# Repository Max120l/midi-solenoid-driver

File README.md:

# midi-solenoid-driver — direct MIDI fork

A fork of [willemcvu/midi-solenoid-driver](https://github.com/willemcvu/midi-solenoid-driver)
that lets the solenoid driver board accept **standard MIDI directly**, with no
interface board in between, and adds **peak-and-hold** solenoid drive,
**selectable MIDI channel**, **optional velocity response**, and **defensive
handling of badly-formed MIDI**.

All hardware in this repository — the driver PCB, the schematics, the gerbers,
the photographs — is Willem Hillier's original work, unchanged. This fork only
replaces the firmware that runs on it.

---

## Why this fork exists

The upstream project is a driver board plus a companion USB-to-serial interface
board. The driver board doesn't speak MIDI; it speaks 38400-baud MIDI-*like*
serial, and the interface board is what turns real MIDI into that. Upstream's
interface work stalled — the `wifi_native_midi` firmware is committed as "not
working" and the repository has had no commits since October 2020. Attempts to
reach the original author about it went unanswered.

Rather than finish the missing interface board, this fork moves the job onto the
driver board itself. The ATmega328PB decodes 31250-baud MIDI on the same RJ12
input pin using the Arduino MIDI Library, so a MIDI source connects straight to
the driver board.

## What's different

| | Upstream `midiSolenoidDriver` | This fork's `midiSolenoidDriverDirectMIDI` |
|---|---|---|
| Input | 38400 baud MIDI-over-serial, needs the interface board | 31250 baud standard MIDI, direct |
| Parsing | Hand-rolled byte-by-byte state machine | Arduino MIDI Library on the hardware UART |
| Running status | Mishandled | Handled |
| Solenoid drive | Full current for the whole note | Peak-and-hold, phase-staggered across channels |
| Velocity | Ignored | Optionally scales pull-in time |
| Note offset | 7-bit DIP switch, 1-note steps | Same, plus a 3-switch fallback mode |
| MIDI channel | 4-bit analog DIP switch | Fixed, DIP-read, or omni |
| Malformed MIDI | Notes can stick on | All-notes-off, stop, reset, and a stuck-note watchdog |

Upstream's original firmware is still here, untouched, in
[`firmware/midiSolenoidDriver/`](firmware/midiSolenoidDriver/). If you have the
USB interface board and it works for you, use that one.

## Hardware

Unchanged from upstream. See [`README-upstream.md`](README-upstream.md) for the
original project description, board photos, and daisy-chaining details.

- Driver board: [`hardware/midi-solenoid-driver/`](hardware/midi-solenoid-driver/)
- MCU: ATmega328PB
- 16 solenoid outputs, "OUTPUTS 1-16" on the silkscreen

[`hardware/HARDWARE-NOTES.md`](hardware/HARDWARE-NOTES.md) records how both DIP
switch blocks are actually wired -- including why the small block shows only two
GPIO connections on a multimeter, and why switch 8 of the large block does
nothing -- and how to deal with the schematic's missing symbol cache.

### MIDI input wiring

MIDI arrives on **pin 0 (RXD0)**, the ATmega's hardware UART receive pin — the
same pin upstream used. Feed it a **conventional, non-inverted MIDI signal**:
idle high, standard UART polarity, which is what a correctly-wired optocoupler
front end produces.

If your input idles *low*, the signal is inverted and the UART will never frame
a byte — it sees a permanent break condition. **The symptom is total silence:
the board boots, runs its exercise routine, and ignores every note.** The right
fix is the wiring, but there is an escape hatch for testing:

```cpp
#define MIDI_INPUT_POLARITY MIDI_INPUT_INVERTED
```

The AVR's USART has no receive-invert bit, so inverting in firmware means
abandoning the hardware UART for `SoftwareSerial` in inverse-logic mode.

**Treat that as a bench workaround, not a destination.** `SoftwareSerial`
receives each byte by busy-waiting through it with interrupts disabled — about
320 µs at 31250 baud, which at 8 MHz is a quarter of the CPU's entire budget
for that stretch. A byte arriving during another byte is lost, which is exactly
what dense MIDI produces, and `loop()` stalls meanwhile so the hold PWM gets
rougher too. Costs about 500 bytes of flash. Fine for proving a few notes;
not what you want under a full chest.

#### Fixing it in hardware instead

Invert the signal before it reaches pin 0 and you keep the hardware UART.
Speed is irrelevant here — a bit is 32 µs at 31250 baud, so any logic family
has thousands of times the margin it needs. Choose for signal quality:

- **74HC14**, a Schmitt-trigger hex inverter. The best pick: it inverts *and*
  squares up the lazy edges an optocoupler with a large pull-up tends to
  produce.
- **74HCT04** if you would rather not use a Schmitt — CMOS input currents with
  TTL-compatible thresholds.
- **A single NPN transistor**, which is usually already in the drawer:

```
  opto out ──[4.7k]──┬── B                      +5V
                     │                           │
                   [10k]      2N3904           [1k]
                     │        E ── GND           │
                    GND       C ─────────────────┴──── to pin 0 (RXD0)
```

The 10k from base to ground matters more than it looks: it holds the
transistor off if the input ever floats, so the output idles **high** — which
a UART reads as "no data" rather than as a break condition.

Tie unused gate inputs of a logic IC to GND or Vcc; floating CMOS inputs
oscillate. Power either option from the board's own 5 V rail.

To verify before connecting: with MIDI idle and nothing playing, the inverter
output should sit **high**, near 5 V. If it idles low, it is still inverted.

The firmware disables the UART **transmitter** while keeping the receiver:

```cpp
UCSR0B &= ~(1 << TXEN0);
```

Several boards share the RJ12 line, and none of them should be able to drive
it. Upstream does the same thing for the same reason. Two consequences worth
knowing:

- **There is no serial debug output.** If you want `Serial.print` while
  bench-testing, comment that line out — but do not do so with the board
  connected to a shared bus, because it will fight every other board on it.
- It also frees pin 1 to be read as a DIP switch input, which is why the
  switches are configured *after* the UART in `setup()`.

Flashing over the bootloader still works normally.

## Configuration

Everything configurable sits in one block at the top of the sketch. It comes
in two kinds: **build-time choices** — which switches mean what, where the MIDI
channel comes from, input polarity — that describe the hardware and need a
reflash to change; and **tuning parameters** — pull-in and hold drive, the
watchdog, the exercise routine — that describe the instrument and are
**adjustable at runtime over MIDI**, see
[Runtime configuration over MIDI](#runtime-configuration-over-midi). The values
in the sketch for the second kind are compiled defaults, not the last word.

### Note offset — which 16 notes this board plays

```cpp
#define NOTE_OFFSET_MODE OFFSET_COARSE3
```

| Mode | Switches used | Steps | Use when |
|---|---|---|---|
| `OFFSET_FULL7` | all 7 of the large DIP block | 1 note | Normal, undamaged hardware |
| `OFFSET_COARSE3` | switches 1-3 only | 16 notes | The other four switches are dead |

**This fork defaults to `OFFSET_COARSE3`**, because the boards it is maintained
against have a damaged large DIP block with only three working switches. If
your switches are all good — which they should be on a board you have just
built — set `OFFSET_FULL7` instead. Nothing else needs to change.

`OFFSET_FULL7` is upstream's mapping, restored: switches 1-7 are worth
+1, +2, +4, +8, +16, +32, +64 respectively, active-low, so any base note from
0 to 127 is reachable. The board responds to `baseNote` through
`baseNote + 15`.

`OFFSET_COARSE3` re-weights the three surviving switches to +16, +32 and +64,
giving base notes 0, 16, 32 … 112. One board's worth of notes per step, so a
chain can still address the whole keyboard — just not at arbitrary offsets.

### MIDI channel

```cpp
#define CHANNEL_SOURCE CHANNEL_FIXED
const byte fixedChannel = 1;
```

| Mode | Behaviour |
|---|---|
| `CHANNEL_FIXED` | Uses `fixedChannel`, 1-16 |
| `CHANNEL_DIP` | Reads the 4-bit small DIP block, upstream's `readSmallDip()` ported back |
| `CHANNEL_OMNI` | Responds on every channel |

`CHANNEL_DIP` reads two analog pins, two switches each, using upstream's
voltage thresholds — that block isn't wired to four digital pins. Upstream's
mapping is 0-indexed; this firmware adds 1, so the switches read as the channel
number your DAW displays.

### Velocity response

```cpp
#define VELOCITY_SOURCE VELOCITY_OFF
```

| Mode | Behaviour | Needs |
|---|---|---|
| `VELOCITY_OFF` | Every note gets the full pull-in time | — |
| `VELOCITY_ON` | Pull-in time scales with velocity | — |
| `VELOCITY_SMALLDIP` | Read one bit of the small DIP block at boot | Channel not from the small DIP |
| `VELOCITY_SWITCH` | Read large-DIP switch 4 (pin 18) at boot | `OFFSET_COARSE3` |

When enabled, velocity scales the pull-in time between `peakDurationMin`
(15 ms) and `peakDurationMax` (40 ms). Harder notes pull in for longer and
therefore hit harder — meaningful on a struck instrument, meaningless on an
organ valve, which is simply open or shut. Hence the default of off.

**If you want velocity on a physical switch, `VELOCITY_SMALLDIP` is normally
the one to use.** Under `OFFSET_FULL7` every switch of the large DIP block is
part of the note offset, so there is no spare one there — but if the MIDI
channel is fixed in firmware, the whole small DIP block is idle, and
`velocitySmallDipBit` picks which of its four switches to read.

`VELOCITY_SWITCH` is the alternative for a board running `OFFSET_COARSE3`,
where large-DIP switches 4-7 are unused anyway.

These constraints are enforced at compile time. Asking for `VELOCITY_SWITCH`
alongside `OFFSET_FULL7`, or `VELOCITY_SMALLDIP` alongside `CHANNEL_DIP`, fails
the build with a message telling you which switches collided — rather than
flashing cleanly and behaving strangely on the bench.

### Stuck-note watchdog

```cpp
30,    // maxNoteSeconds   -- in factoryDefaults; runtime: CC 24, 0 disables
```

Any solenoid held longer than this is force-released. Set to `0` to disable —
but understand what you are turning off: with the watchdog disabled, one
missing note-off leaves a valve open until you power-cycle the board. 30
seconds is longer than almost any real note. Raise it if your music genuinely
holds notes longer than that.

### Power-up valve exercise

```cpp
2,     // exerciseCycles   -- in factoryDefaults; runtime: CC 25, 0 disables
const int exerciseOnTime  = 60;  // ms energised
const int exerciseOffTime = 60;  // ms released
```

Fires every output in turn at boot, at full power, before wind is applied.

The point is **pluck** — the adhesion between a valve and its seat after the
instrument has sat closed. On a lightly loaded valve this can be the largest
single force the solenoid has to overcome, and it is worst on the very first
cycle after a rest, which is exactly the note you least want to fail. Working
the valves loose while the chest is unpressurised costs nothing and no pipe
speaks.

It is sequential rather than simultaneous on purpose. One solenoid at a time
draws a sixteenth of the current, and you hear each output fire in order — so a
dead channel, a swapped connector or a stuck valve announces itself at every
power-up. It doubles as a power-on self test.

Full power is used regardless of `peakDutyPercent`, since breaking stiction is
the one job that genuinely wants maximum force, and one-at-a-time makes the
current draw trivial.

The defaults take `2 × 16 × 120 ms` ≈ **3.8 seconds**. The UART is unattended
during that time, so the receive buffer is discarded afterwards to stop a
part-received message sounding a note the instant the loop opens. Set
`exerciseCycles` to 0 to disable, in which case the shorter boot heartbeat runs
instead and the whole routine is optimised out of the build.

### Runtime configuration over MIDI

The tuning parameters are adjustable while the boards run, by control changes
on a **dedicated configuration channel**, and can be saved to each board's
EEPROM so they survive a power cycle. A board built into an instrument never
needs reflashing to retune it. The Pi-side tool is
[`tools/organ-config/`](tools/organ-config/):

```bash
python organ_config.py --port "USB MIDI" --peak 60 --hold 25 --save
```

| CC | Setting | Range on the wire | Firmware clamps to |
|---|---|---|---|
| 20 | select board | 0–112 = the board with that base note; 113–127 = all | |
| 21 | `peakDutyPercent` | 0–127 | 1–100 |
| 22 | `holdDutyPercent` | 0–127 | 0–`HOLD_DUTY_MAX_PERCENT` (40) |
| 23 | `peakDurationMs` | 0–127 | 1–`PEAK_DURATION_MAX_MS` (127) |
| 24 | `maxNoteSeconds` | 0–127 | as sent; 0 disables the watchdog |
| 25 | `exerciseCycles` | 0–127 | 0–`EXERCISE_CYCLES_MAX` (10) |
| 26 | command | 1 save · 2 reload · 3 factory | |

All on `CONFIG_CHANNEL`, which is **16**; music is on channel 1. That
separation is what stops a stray CC inside a song from retuning the organ
mid-piece — and the arranger's output contains no CCs at all regardless.
Panic messages (CC 120 and 123) are honoured on *every* channel.

**Changes take effect immediately, including on notes already sounding.** That
is deliberate, and it is what makes tuning by ear possible: hold a chord and
step the hold duty down until a valve drops out, back off, save.

**The clamps are the safety.** The boards cannot transmit, so they cannot
report that a value would cook the coils — they can only refuse it. Every
value, whether it arrives by MIDI or is read back from EEPROM, passes through
the same clamps, and the ceilings are compile-time constants sized for
duty-limited solenoids. Raise them only for coils rated for it.

**Save is explicit, and acknowledged.** Settings live in RAM until command 1
writes them to EEPROM — EEPROM has a finite number of writes and live tuning
would otherwise chew through it. A save is acknowledged by a click on output 1
if that output is idle; under wind, a chirp from the board's lowest pipe, and
four boards saving together answer as a four-note chord. Set `CONFIG_ACK` to 0
for silence. At power-up a board loads its EEPROM record if the magic number,
layout version and checksum all agree, and the compiled defaults otherwise.

**A board selection expires.** CC 20 with a base note makes only that board
listen; it reverts to all boards after a quiet minute, so a forgotten selection
cannot strand one. In practice, with identical solenoids on every board, you
address all of them.

`CONFIG_ENABLED 0` compiles the whole layer out, saving about 650 bytes.

## Daisy-chaining several boards

Boards chain over RJ12 and all see the same MIDI stream. Each one is told which
16 notes are *its* by its DIP switches. All boards run identical firmware.

A four-board chain under the default `OFFSET_COARSE3`, covering MIDI notes
48-111 (C3 to D#8). Base notes are limited to multiples of 16, which is exactly
one board's worth, so four boards tile without gaps:

| Board | Base note | Notes covered | Switches closed |
|---|---|---|---|
| 1 | 48 | 48-63 | 1, 2 |
| 2 | 64 | 64-79 | 3 |
| 3 | 80 | 80-95 | 1, 3 |
| 4 | 96 | 96-111 | 2, 3 |

This instrument's chain sits one step lower than that table: board 1 with
every switch open at base note **0**, then 16, 32 and 48, so solenoid *N*
(numbered 1–64, as on the layout sheet) fires on MIDI note *N − 1*. The
arranger's definition, `tools/organ-arranger/instrument/organ.yaml`, records
that as `solenoid_1_note: 0` and does the subtraction itself; the table above
is the same idea shifted up three octaves.

The same chain under `OFFSET_FULL7`, where any base note is reachable — here
placed at 36-99 (C2 to D#7) instead:

| Board | Base note | Notes covered | Switches closed |
|---|---|---|---|
| 1 | 36 | 36-51 | 6, 3 |
| 2 | 52 | 52-67 | 6, 5, 3 |
| 3 | 68 | 68-83 | 7, 3 |
| 4 | 84 | 84-99 | 7, 5, 3 |

**Verified with four boards**, at base notes set by their DIP switches, sharing
one MIDI signal down the chain and playing arranged music from a Raspberry
Pi. The same binary runs on every board — the note offset is read from the
switches at boot, so nothing in the firmware needs to differ between them.

Points that matter with more than one board:

- **Every board must have its transmitter disabled.** The firmware does this,
  but if you comment it out for debugging on one board, take that board off the
  bus first.
- **Channel.** With `CHANNEL_FIXED` every board listens on the same channel,
  which is what you usually want — they're separated by note range, not by
  channel. Use `CHANNEL_DIP` if you want per-board channels instead.
- **Power.** Four boards is up to 64 solenoids. The phase staggering below
  reduces the peak draw *within* one board; it does not coordinate boards with
  each other. Size the supply for the realistic worst case.

## Building and flashing

Arduino IDE, or `arduino-cli`:

- **Board:** ATmega328PB. Requires a core with 328PB support — e.g.
  [MiniCore](https://github.com/MCUdude/MiniCore).
- **Libraries:** [MIDI Library](https://github.com/FortySevenEffects/arduino_midi_library)
  by Forty Seven Effects.

Open [`firmware/midiSolenoidDriverDirectMIDI/midiSolenoidDriverDirectMIDI.ino`](firmware/midiSolenoidDriverDirectMIDI/midiSolenoidDriverDirectMIDI.ino)
and upload.

Verified building with MiniCore 3.1.3 and MIDI Library 5.0.2, in every
combination of the configuration options above:

```
arduino-cli compile --fqbn MiniCore:avr:328:variant=modelPB,clock=8MHz_internal \
  firmware/midiSolenoidDriverDirectMIDI
```

Which yields, comfortably inside the 328PB:

```
Sketch uses 5896 bytes (18%) of program storage space. Maximum is 32384 bytes.
Global variables use 569 bytes (27%) of dynamic memory, leaving 1479 for locals.
```

**Confirmed running on hardware**, not merely compiling: an ATmega328PB at
8 MHz internal, MIDI decoded on the hardware UART, boot exercise routine and
note handling both working. The optocoupler feeding it was inverting, corrected
with an external NPN inverter as described under
[MIDI input wiring](#midi-input-wiring) — that is the sanctioned fix, in
preference to the firmware workaround.

### ⚠️ The clock setting is not optional

**This board has no crystal.** `XTAL1`/`PB6` and `XTAL2`/`PB7` are wired as
solenoid outputs CTRL5 and CTRL6, so the oscillator pins are unavailable and
the ATmega runs from its internal RC oscillator.

MiniCore defaults to `clock=16MHz_external`. Build with that default and flash
it to a chip fused for 8 MHz internal, and `F_CPU` is wrong by a factor of two:

- `Serial.begin(31250)` actually produces **15625 baud** — no MIDI is received
  at all
- `millis()` and `micros()` run at half speed, so the 40 ms peak becomes 80 ms,
  the hold PWM drops to 250 Hz, and the watchdog stretches to 60 s
- The boot heartbeat still clicks, just slowly — so the board looks alive while
  being completely deaf, which is a miserable thing to debug

Set the clock explicitly, and make it match the fuses actually programmed into
your chips. In the Arduino IDE that is Tools → Clock → "Internal 8 MHz".

31250 baud divides exactly at both 8 and 16 MHz (`UBRR` = 15 and 31
respectively), so there is no divisor rounding error at either. The whole error
budget belongs to the RC oscillator, which is factory-calibrated to about ±1%
but drifts with temperature and supply. UART framing tolerates roughly ±2%, so
this works — it worked for upstream too — but if you ever see occasional
garbled MIDI in a cold or hot organ chamber, oscillator drift is the first
suspect, not the firmware.

Running at 8 MHz also makes `loop()` timing tight enough to matter: see
[Phase staggering](#phase-staggering).

On boot the valve exercise routine runs, or if disabled, output 1 clicks once
for 150 ms as a heartbeat.

## Tuning peak-and-hold

```cpp
const Settings factoryDefaults = {
  100,   // peakDutyPercent   runtime: CC 21
  25,    // holdDutyPercent   runtime: CC 22   (500 us of the 2000 us period)
  40,    // peakDurationMs    runtime: CC 23
  30,    // maxNoteSeconds    runtime: CC 24
  2,     // exerciseCycles    runtime: CC 25
};
const int peakDurationMin = 15;   // ms at lowest velocity, when scaling; build-time
const int pwmPeriod       = 2000; // us, PWM period for both phases (500 Hz); build-time
```

These are compiled defaults. Once the boards are in the instrument, tune them
over MIDI and save — see
[Runtime configuration over MIDI](#runtime-configuration-over-midi).

`peakDurationMax` needs to be long enough for the solenoid to physically pull
in — too short and it will buzz or fail to seat under load. `pwmOnTime` needs
to be high enough to *keep* it seated but low enough that the coil doesn't
overheat on sustained notes.

Tune in that order: raise the peak until every solenoid reliably pulls in under
real load, then lower `pwmOnTime` in steps until one drops out, then back off
by a comfortable margin. Small valve solenoids will often hold far below 40%.

These values are a working starting point, not a universal answer.

### Driving the pull-in less hard

```cpp
100,   // peakDutyPercent   -- in factoryDefaults; runtime: CC 21
```

100 means solid DC for the whole peak window. Lower values PWM the pull-in as
well, at the same 500 Hz and with the same per-channel stagger.

**This is the single most effective lever on supply current**, because the
pull-in is the only time every energised channel draws full current
simultaneously — the hold phase is already staggered and duty-limited. Reducing
it also brings the stagger to bear on the attack, which at 100% it cannot
touch.

Reduce it when the solenoids are overspecced for what they move, which is
common: a 22 W actuator shifting a small valve does not need 22 W to seat it.
Tune on the bench under real load — reduce until a solenoid seats sluggishly or
not at all, then back off generously. Too low is worse than too high: notes
fail silently under load, which is far harder to diagnose later than a supply
that runs warm.

Bounds are checked at compile time; 0 or 101 fails the build.

### Worked example: an overspecced, duty-limited solenoid

A U0530S tubular solenoid driving a small valve. Datasheet says 12 V, 6.5 Ω,
1.8 A, 22 W, **rated 10% duty cycle**; **measured coil resistance is closer to
7 Ω**, which is what the figures below use — 1.71 A and 20.6 W at 12 V.

Force falls roughly with the square of coil current, so the numbers move very
differently from the current:

| `peakDutyPercent` | Coil current | Pull-in force | 16-ch attack | 20-ch | 64-ch |
|---|---|---|---|---|---|
| 100 | 1.71 A | 100% | 27.4 A | 34.3 A | 110 A |
| 80 | 1.35 A | 62% | 17.3 A | 21.6 A | 69 A |
| 70 | 1.17 A | 47% | 13.1 A | 16.4 A | 52 A |
| 60 | 0.99 A | 33% | 9.5 A | 11.9 A | 38 A |
| 50 | 0.81 A | 22% | 6.5 A | 8.1 A | 26 A |

The force column is independent of coil resistance — it depends only on the
ratio of held current to full current, which the duty cycle sets. Only the
amperages moved.

A solenoid rated to pull 700 g moving a valve needing perhaps 50 g still has
roughly a 4:1 margin at 60% duty. Three times less supply current for margin
you were never using.

Note how much peak-and-hold is already doing before you touch this: at 100%,
sixteen channels attack at 27.4 A and settle to **4.0 A** holding.

**Capacitors cannot rescue the attack.** C = I·t/ΔV, so covering 34 A for a
40 ms peak within 1 V of droop needs about 1.4 farads. Bulk capacitance tames
switching edges only — the supply must genuinely deliver the attack, or the
attack must come down.

### Solenoids with a duty-cycle rating

Many cheap actuators are rated for intermittent use — "10% ED", "duty cycle
10%" — meaning they are not built to stay energised. Treat the rating as a
thermal budget: **rated wattage × rated duty** is roughly the average
dissipation that produces the quoted temperature rise. For the measured 7 Ω
coil that is 20.6 W at 12 V, so the budget is about **2.1 W**.

Hold dissipation, allowing for the flyback diode clamping the coil during the
off portion:

| `pwmOnTime` | Duty | Coil current | Hold force | Dissipation | vs 2.1 W |
|---|---|---|---|---|---|
| 800 | 40% | 0.63 A | ~93 gf | 2.74 W | 133% — over |
| 700 | 35% | 0.54 A | ~70 gf | 2.00 W | 97% |
| 600 | 30% | 0.44 A | ~47 gf | 1.38 W | 67% |
| **500 (default)** | 25% | 0.35 A | ~30 gf | 0.87 W | 42% |
| 400 | 20% | 0.26 A | ~17 gf | 0.48 W | 23% |

Measuring 7 Ω rather than 6.5 Ω barely moves these proportions, since both the
dissipation and the budget scale the same way with resistance.

#### Measured, on a bench with unloaded solenoids

| `pwmOnTime` | Predicted, solenoid only | Measured, whole board | Difference |
|---|---|---|---|
| 800 | 250 mA | 330 mA | 80 mA |
| 400 | 53 mA | 100 mA | 47 mA |

The gap is roughly constant rather than proportional, so it is fixed overhead —
the ATmega and the RECOM regulator, not the coil. Subtract about 50 mA and the
model matches at both points.

**Why the default is 500 and not 400.** 400 held fine unloaded, but a bench
solenoid has no spring, no valve, and gravity helping it stay in. The return
spring measures around 50 gf, and it stiffens as the valve opens, so the real
holding requirement is perhaps 10–30 gf once gravity on the plunger is
subtracted. 400 offers ~17 gf against that; 500 offers ~30 gf.

The failure mode of too little hold is a valve dropping out partway through a
held note — intermittent, audible, and unpleasant to diagnose months later.
Start at 500 with real springs, and only come down once it has proven itself.

What saves you is thermal mass: the coil integrates over minutes, so what
matters is the average across a passage, not any single note. Ordinary playing
with notes down a third of the time is comfortable even at 40%.

The real hazards are a **drone or pedal point held for minutes**, and a **stuck
note**. On duty-limited solenoids the stuck-note watchdog stops being a
convenience and becomes a thermal safety feature — consider shortening
`maxNoteDuration` well below its 30 s default, and note that it will also cut
off any legitimately long note, which is a genuine trade-off rather than a free
win.

### Phase staggering

```cpp
const int pwmPhaseStep = pwmPeriod / numSolenoids; // us, 125 us per channel
```

Each channel's hold PWM is offset by `i * pwmPhaseStep`, so the 16 channels'
on-times are spread evenly across the 2 ms period instead of all starting
together. Every coil still gets the same duty and the same holding force; what
changes is the peak the supply has to deliver.

Simulating one full 2 ms period with all 16 channels held, at 40% duty:

| | In phase (`pwmPhaseStep = 0`) | Staggered (125 us) |
|---|---|---|
| Duty per coil | 40% | 40% |
| Mean coils on | 6.40 | 6.40 |
| **Peak coils on** | **16** | **7** |
| Load over the period | 0 coils for 60% of it, then all 16 for 40% | 6 coils for 60% of it, 7 for 40% |

Same average power, same holding force, less than half the peak draw, and a
nearly flat load instead of a hard square wave at 500 Hz. Setting
`pwmPhaseStep` to `0` restores the original behaviour if you want to compare.

There is also a small per-board offset derived from the note offset, so chained
boards don't stagger identically. Don't lean on it: each board runs from its
own internal RC oscillator, which varies by a percent or two part to part, so
chained boards drift relative to one another continuously and would never stay
in lockstep anyway. It is a free nudge, not load management.

### Why the offsets are precomputed

At 8 MHz, `loop()` speed is not a detail. A 32-bit modulo per channel per pass
— sixteen of them — costs more than everything else in the loop combined, and
would push the loop period past the 125 µs phase step it is trying to resolve.
A stagger finer than the loop that implements it is no stagger at all.

So each channel's offset is computed once in `setup()` into `channelPhase[]`,
and the hot path uses 16-bit arithmetic with a single conditional subtraction:

```cpp
unsigned int cyclePosition = cycleBase + channelPhase[i];
if (cyclePosition >= pwmPeriod) cyclePosition -= pwmPeriod;
```

Exactly one 32-bit modulo survives, computing `cycleBase` once per pass. The
result is arithmetically identical to the obvious version — verified across all
32000 (position, channel) combinations — at 32 bytes of RAM.

## Robustness with badly-formed MIDI

A solenoid left energised is worse than a missed note: it drones, it heats the
coil, and it heats the driver. Everything here fails toward "off".

**Note-off expressed as velocity 0.** Handled — a note-on with zero velocity is
treated as note-off, per the spec. This is how most sequencers express note-off
in the first place, and how a note "removed" by zeroing its velocity arrives.

**Overlapping and duplicate notes.** A second note-on for a note already
sounding restarts its pull-in, so the note re-articulates rather than being
ignored. A single note-off then releases it, regardless of how many note-ons
arrived. This is deliberately *not* reference-counted: if a file sends two
note-ons and only one note-off, counting would hold the valve open forever,
whereas last-off-wins simply releases it. The failure mode is a note that stops
slightly early, not a valve that never closes.

**Panic messages.** CC 120 (All Sound Off), CC 123 (All Notes Off), MIDI Stop
and System Reset all release every solenoid. Sequencers emit these on stop, on
panic, and at the end of a file, and honouring them is the difference between a
clean stop and a chord left droning.

**Note-offs that never arrive.** The watchdog force-releases anything held past
`maxNoteDuration`. This is the backstop for a truncated file, a crashed
sequencer, or a cable pulled mid-note.

**Running status and dense streams.** Upstream's hand-rolled parser mishandled
running status, which tightly-packed files use heavily. The MIDI library
handles it correctly, along with interleaved real-time bytes and message types
this board ignores. Reception is on the hardware UART, which is interrupt-driven
and buffered — the previous `SoftwareSerial` implementation busy-waited through
each byte with interrupts disabled for roughly 320 us, during which a second
byte arriving was simply lost. That was the real hazard at high note density.

**A note on tempo.** Tempo changes are a Standard MIDI File concept: meta-events
resolved by whatever plays the file. They never reach this board, which only
ever sees note and control messages already placed in time by the player. There
is nothing for the firmware to do about them, and any firmware claiming to
handle tempo would be doing nothing. What tempo *does* affect is how densely
events arrive — and that is exactly what moving to the hardware UART addresses.

## Known limitations

Things this fork does not yet do. Contributions welcome.

- **No aftertouch or polypressure.** Stubbed but unimplemented upstream too.
- **Velocity affects pull-in time only.** It does not vary holding force, and
  on a valve it has no acoustic effect at all.
- **The per-board PWM offset is below `loop()` resolution**, as described above.
- **Verified with four daisy-chained boards** playing arranged music from a
  Raspberry Pi over one single-ended MIDI line, at base notes 0/16/32/48,
  driving 64 solenoids on a common star ground. Supply draw at 60% pull-in
  and 25% hold: about 1 A averaged over a tune, peaks around 3 A, across a
  dozen arrangements with no valve failing to open or to close. Untested:
  longer chains, and chains without a common ground — see
  [Daisy-chaining several boards](#daisy-chaining-several-boards).
- **Four `unused parameter` warnings** under `-Wall -Wextra`, from MIDI library
  callback signatures that require arguments this firmware doesn't read. They
  do not appear in a default build.

## Tools

[`tools/organ-arranger/`](tools/organ-arranger/) turns a multi-track MIDI file
authored in a DAW into the single-track, single-channel file these boards
play, where every note is one solenoid. The mapping is per track —
on a band organ the same note number on a different track is a different
pipe — and comes from the instrument's **layout spreadsheet**, which
`layout_to_organ.py` turns into the organ definition; the sheet is the source
of truth. The arranger then makes each solenoid physically playable — merging
overlaps, enforcing minimum note lengths and re-articulation gaps — pulses
every register reset before and after the music so their state is always
known, and writes a report of every note it dropped, merged, stretched or
trimmed. This organ's own sheet, generated definition and an all-notes sample
file live in [`tools/organ-arranger/instrument/`](tools/organ-arranger/instrument/).
A third tool, `organ_transcribe.py`, goes one step earlier: it takes an
ordinary multi-track MIDI tune in any key and arranges it *for* the organ —
finding the transposition that best fits the pipes, assigning voices to ranks,
folding lines into each rank's compass, mapping the drums, beating the
leader's arm on the downbeats — with every choice in an editable plan.
Python, on `mido`; see its README.

[`tools/player/`](tools/player/) is the playback engine on the Pi: arranged
files down the UART one after another, from files, folders or playlists,
with tempo, the pause between songs, shuffle and repeat, a clean skip, a
status file, and the bellows pump's relay. [`tools/organ-web/`](tools/organ-web/)
is the front desk on top of it: one web page for a touchscreen on the case
and for any phone on the Wi-Fi -- the queue, the library, saved playlists,
uploads that run the arranger, the pump, a reset button and a touch version
of the keys tester. The player runs as its child and keeps playing if the
page does not.

[`tools/organ-config/`](tools/organ-config/) retunes the boards over MIDI —
pull-in duty and duration, hold duty, watchdog, exercise passes — from the Pi
or anything with a MIDI output, and saves the result to each board's EEPROM.
No reflashing once the boards are in the instrument. See
[Runtime configuration over MIDI](#runtime-configuration-over-midi).

## Ideas and open questions

[`IDEAS.md`](IDEAS.md) parks work that is thought about but not decided: the
Raspberry Pi player, configuring boards over the MIDI bus rather than by DIP
switch, and the interaction between the boot exercise routine and blower
timing.

## Credit and licence

Original project, hardware and firmware: **Willem Hillier**
(<https://github.com/willemcvu/midi-solenoid-driver>), MIT licensed, © 2019.

MIT licence retained — see [LICENSE](LICENSE). Upstream's copyright notice
stays in place; this fork's modifications are offered under the same terms.

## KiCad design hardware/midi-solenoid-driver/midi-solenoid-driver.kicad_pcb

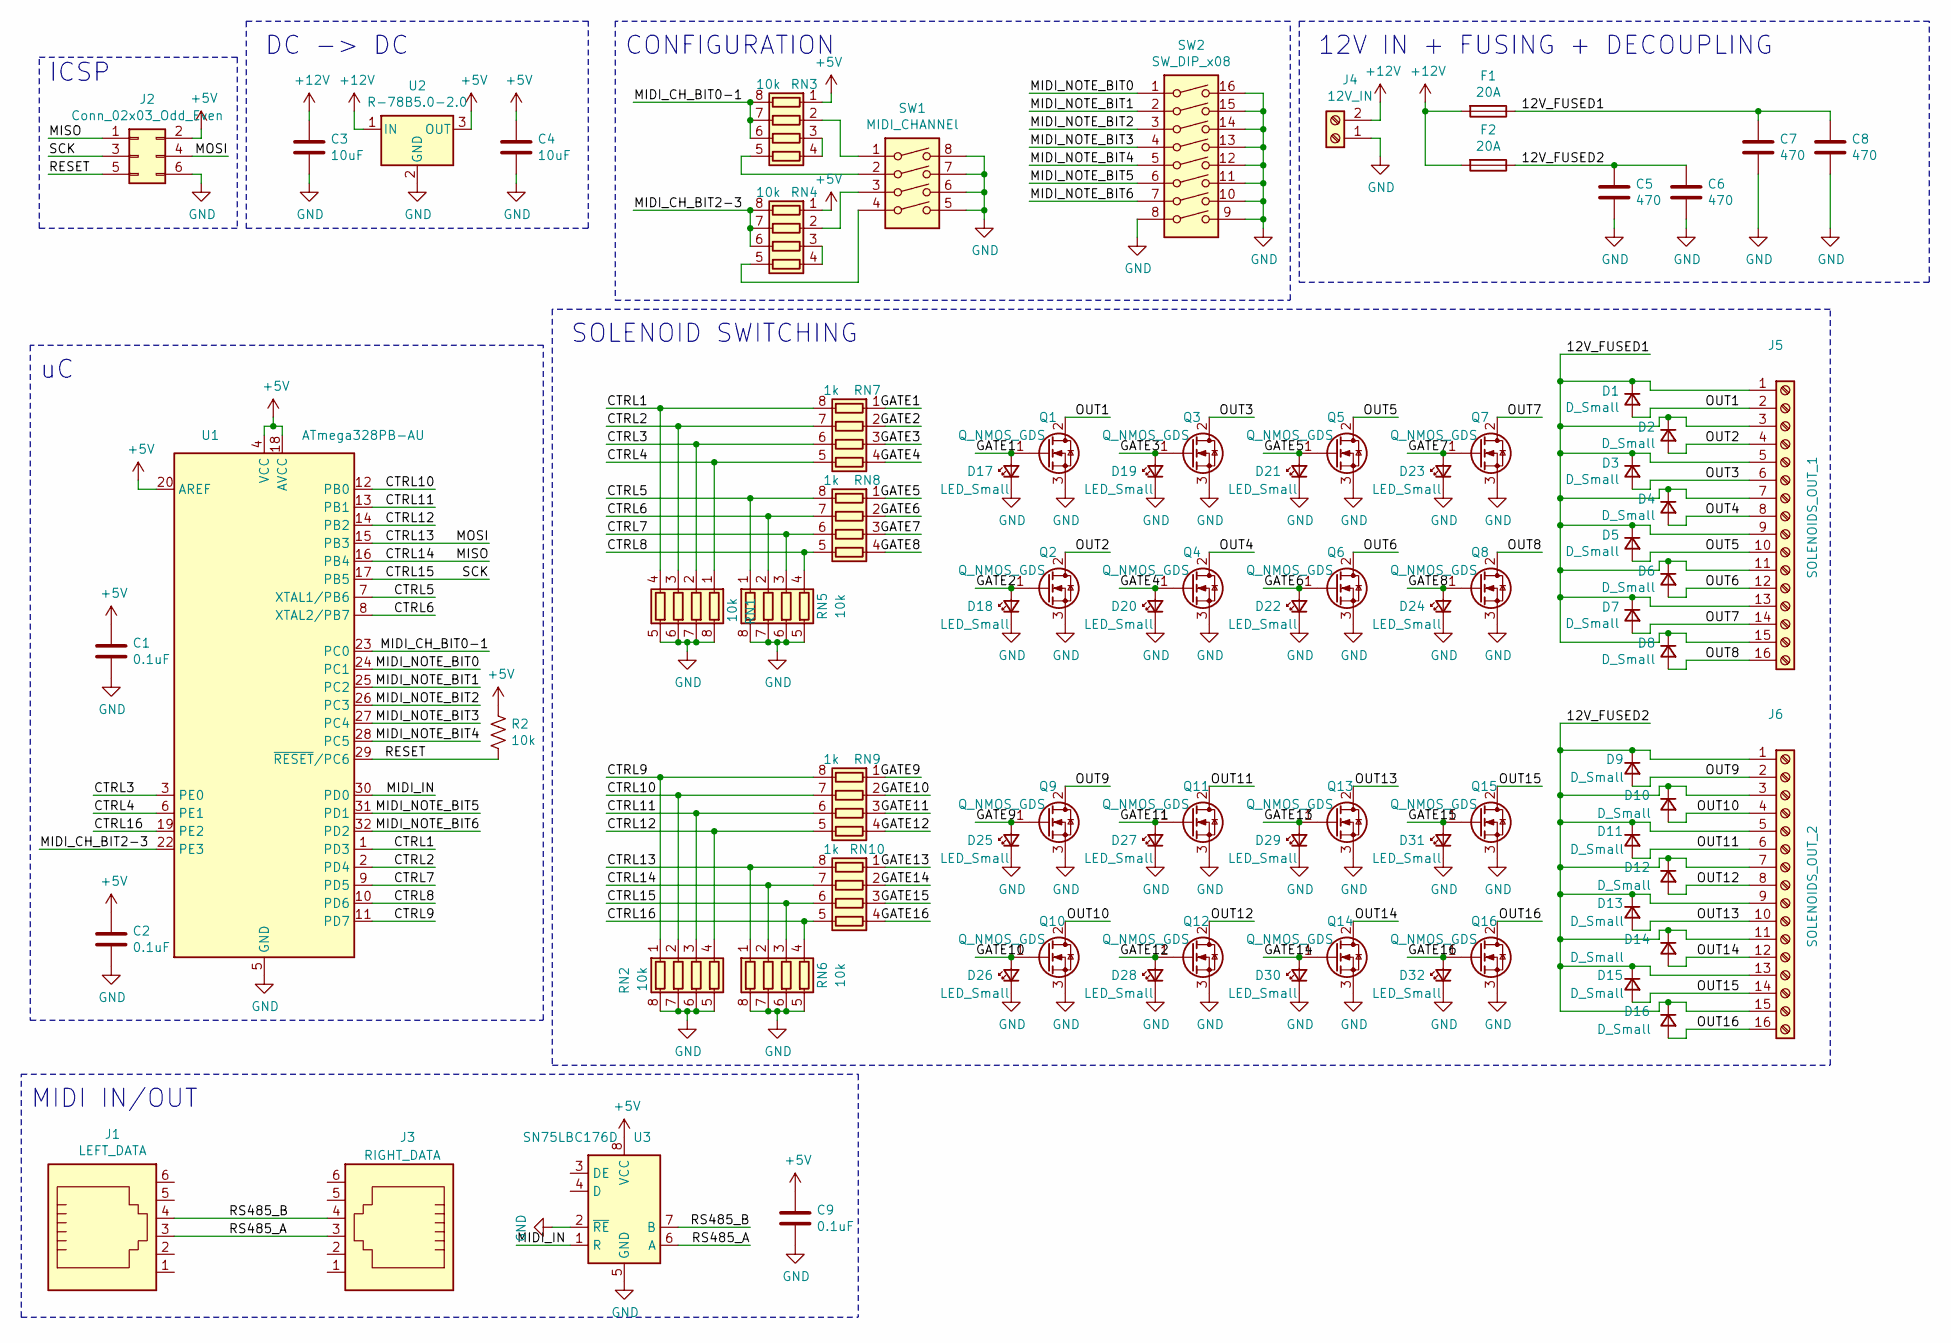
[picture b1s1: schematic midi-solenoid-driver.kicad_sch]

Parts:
C1, C2, C9: 0.1uF; C_0603_1608Metric
C3, C4: 10uF; C_0805_2012Metric
C5, C6, C7, C8: 470; C_Elec_10x10.2
D1, D2, D3, D4, D5, D6, D7, D8, D9, D10, D11, D12, D13, D14, D15, D16: D_Small; D_SMA
D17, D18, D19, D20, D21, D22, D23, D24, D25, D26, D27, D28, D29, D30, D31, D32: LED_Small; LED_0603_1608Metric
F1, F2: 20A; Fuseholder_Blade_Mini_Keystone_3568
J1: LEFT_DATA; RJ12_Amphenol_54601
J2: Conn_02x03_Odd_Even; PinHeader_2x03_P2.54mm_Vertical
J3: RIGHT_DATA; RJ12_Amphenol_54601
J4: 12V_IN; TerminalBlock_MetzConnect_Type701_RT11L02HGLU_1x02_P6.35mm_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
J5: SOLENOIDS_OUT_1; TerminalBlock_Phoenix_PT-1,5-16-3.5-H_1x16_P3.50mm_Horizont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
J6: SOLENOIDS_OUT_2; TerminalBlock_Phoenix_PT-1,5-16-3.5-H_1x16_P3.50mm_Horizont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
Q1, Q2, Q3, Q4, Q5, Q6, Q7, Q8, Q9, Q10, Q11, Q12, Q13, Q14, Q15, Q16: Q_NMOS_GDS; TO-252-2
R2: 10k; R_0603_1608Metric
RN1, RN2, RN3, RN4, RN5, RN6: 10k; R_Array_Concave_4x0603
RN7, RN8, RN9, RN10: 1k; R_Array_Concave_4x0603
SW1: MIDI_CHANNEl; SW_DIP_SPSTx04_Slide_6.7x11.72mm_W7.62mm_P2.54mm_LowProfile
SW2: SW_DIP_x08; SW_DIP_SPSTx08_Slide_6.7x21.88mm_W7.62mm_P2.54mm_LowProfile
U1: ATmega328PB-AU; TQFP-32_7x7mm_P0.8mm
U2: R-78B5.0-2.0; Converter_DCDC_RECOM_R-78B-2.0_THT
U3: SN75LBC176D; SOIC-8_3.9x4.9mm_P1.27mm

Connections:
+5V: C1.1, C2.1, C4.1, C9.1, J2.2, R2.1, RN3.1 (R1.1), RN4.1 (R1.1), U1.4 (VCC), U1.18 (AVCC), U1.20 (AREF), U2.3 (OUT), U3.8 (VCC)
+12V: C3.1, F1.2, F2.2, J4.2, U2.1 (IN)
/12V_FUSED1: C7.1, C8.1, D1.1 (K), D2.1 (K), D3.1 (K), D4.1 (K), D5.1 (K), D6.1 (K), D7.1 (K), D8.1 (K), F1.1, J5.1, J5.3, J5.5, J5.7, J5.9, J5.11, J5.13, J5.15
/12V_FUSED2: C5.1, C6.1, D9.1 (K), D10.1 (K), D11.1 (K), D12.1 (K), D13.1 (K), D14.1 (K), D15.1 (K), D16.1 (K), F2.1, J6.1, J6.3, J6.5, J6.7, J6.9, J6.11, J6.13, J6.15
/CTRL1: RN1.4 (R4.1), RN7.8 (R1.2), U1.1 (PD3)
/CTRL2: RN1.3 (R3.1), RN7.7 (R2.2), U1.2 (PD4)
/CTRL3: RN1.2 (R2.1), RN7.6 (R3.2), U1.3 (PE0)
/CTRL4: RN1.1 (R1.1), RN7.5 (R4.2), U1.6 (PE1)
/CTRL5: RN5.1 (R1.1), RN8.8 (R1.2), U1.7 (XTAL1/PB6)
/CTRL6: RN5.2 (R2.1), RN8.7 (R2.2), U1.8 (XTAL2/PB7)
/CTRL7: RN5.3 (R3.1), RN8.6 (R3.2), U1.9 (PD5)
/CTRL8: RN5.4 (R4.1), RN8.5 (R4.2), U1.10 (PD6)
/CTRL9: RN2.1 (R1.1), RN9.8 (R1.2), U1.11 (PD7)
/CTRL10: RN2.2 (R2.1), RN9.7 (R2.2), U1.12 (PB0)
/CTRL11: RN2.3 (R3.1), RN9.6 (R3.2), U1.13 (PB1)
/CTRL12: RN2.4 (R4.1), RN9.5 (R4.2), U1.14 (PB2)
/CTRL13: J2.4, RN6.1 (R1.1), RN10.8 (R1.2), U1.15 (PB3)
/CTRL14: J2.1, RN6.2 (R2.1), RN10.7 (R2.2), U1.16 (PB4)
/CTRL15: J2.3, RN6.3 (R3.1), RN10.6 (R3.2), U1.17 (PB5)
/CTRL16: RN6.4 (R4.1), RN10.5 (R4.2), U1.19 (PE2)
/GATE1: D17.2 (A), Q1.1 (G), RN7.1 (R1.1)
/GATE2: D18.2 (A), Q2.1 (G), RN7.2 (R2.1)
/GATE3: D19.2 (A), Q3.1 (G), RN7.3 (R3.1)
/GATE4: D20.2 (A), Q4.1 (G), RN7.4 (R4.1)
/GATE5: D21.2 (A), Q5.1 (G), RN8.1 (R1.1)
/GATE6: D22.2 (A), Q6.1 (G), RN8.2 (R2.1)
/GATE7: D23.2 (A), Q7.1 (G), RN8.3 (R3.1)
/GATE8: D24.2 (A), Q8.1 (G), RN8.4 (R4.1)
/GATE9: D25.2 (A), Q9.1 (G), RN9.1 (R1.1)
/GATE10: D26.2 (A), Q10.1 (G), RN9.2 (R2.1)
/GATE11: D27.2 (A), Q11.1 (G), RN9.3 (R3.1)
/GATE12: D28.2 (A), Q12.1 (G), RN9.4 (R4.1)
/GATE13: D29.2 (A), Q13.1 (G), RN10.1 (R1.1)
/GATE14: D30.2 (A), Q14.1 (G), RN10.2 (R2.1)
/GATE15: D31.2 (A), Q15.1 (G), RN10.3 (R3.1)
/GATE16: D32.2 (A), Q16.1 (G), RN10.4 (R4.1)
/MIDI_CH_BIT0-1: RN3.6 (R3.2), RN3.7 (R2.2), RN3.8 (R1.2), U1.23 (PC0)
/MIDI_CH_BIT2-3: RN4.6 (R3.2), RN4.7 (R2.2), RN4.8 (R1.2), U1.22 (PE3)
/MIDI_IN: U1.30 (PD0), U3.1 (R)
/MIDI_NOTE_BIT0: SW2.1, U1.24 (PC1)
/MIDI_NOTE_BIT1: SW2.2, U1.25 (PC2)
/MIDI_NOTE_BIT2: SW2.3, U1.26 (PC3)
/MIDI_NOTE_BIT3: SW2.4, U1.27 (PC4)
/MIDI_NOTE_BIT4: SW2.5, U1.28 (PC5)
/MIDI_NOTE_BIT5: SW2.6, U1.31 (PD1)
/MIDI_NOTE_BIT6: SW2.7, U1.32 (PD2)
/OUT1: D1.2 (A), J5.2, Q1.2 (D)
/OUT2: D2.2 (A), J5.4, Q2.2 (D)
/OUT3: D3.2 (A), J5.6, Q3.2 (D)
/OUT4: D4.2 (A), J5.8, Q4.2 (D)
/OUT5: D5.2 (A), J5.10, Q5.2 (D)
/OUT6: D6.2 (A), J5.12, Q6.2 (D)
/OUT7: D7.2 (A), J5.14, Q7.2 (D)
/OUT8: D8.2 (A), J5.16, Q8.2 (D)
/OUT9: D9.2 (A), J6.2, Q9.2 (D)
/OUT10: D10.2 (A), J6.4, Q10.2 (D)
/OUT11: D11.2 (A), J6.6, Q11.2 (D)
/OUT12: D12.2 (A), J6.8, Q12.2 (D)
/OUT13: D13.2 (A), J6.10, Q13.2 (D)
/OUT14: D14.2 (A), J6.12, Q14.2 (D)
/OUT15: D15.2 (A), J6.14, Q15.2 (D)
/OUT16: D16.2 (A), J6.16, Q16.2 (D)
/RESET: J2.5, R2.2, U1.29 (~RESET/PC6)
/RS485_A: J1.3, J3.3, U3.6 (A)
/RS485_B: J1.4, J3.4, U3.7 (B)
GND: C1.2, C2.2, C3.2, C4.2, C5.2, C6.2, C7.2, C8.2, C9.2, D17.1 (K), D18.1 (K), D19.1 (K), D20.1 (K), D21.1 (K), D22.1 (K), D23.1 (K), D24.1 (K), D25.1 (K), D26.1 (K), D27.1 (K), D28.1 (K), D29.1 (K), D30.1 (K), D31.1 (K), D32.1 (K), J2.6, J4.1, Q1.3 (S), Q2.3 (S), Q3.3 (S), Q4.3 (S), Q5.3 (S), Q6.3 (S), Q7.3 (S), Q8.3 (S), Q9.3 (S), Q10.3 (S), Q11.3 (S), Q12.3 (S), Q13.3 (S), Q14.3 (S), Q15.3 (S), Q16.3 (S), RN1.5 (R4.2), RN1.6 (R3.2), RN1.7 (R2.2), RN1.8 (R1.2), RN2.5 (R4.2), RN2.6 (R3.2), RN2.7 (R2.2), RN2.8 (R1.2), RN5.5 (R4.2), RN5.6 (R3.2), RN5.7 (R2.2), RN5.8 (R1.2), RN6.5 (R4.2), RN6.6 (R3.2), RN6.7 (R2.2), RN6.8 (R1.2), SW1.5, SW1.6, SW1.7, SW1.8, SW2.8, SW2.9, SW2.10, SW2.11, SW2.12, SW2.13, SW2.14, SW2.15, SW2.16, U1.5 (GND), U1.21 (GND), U2.2 (GND), U3.2 (~RE), U3.5 (GND)
unnamed: RN3.2 (R2.1), SW1.1
unnamed: RN3.3 (R3.1), RN3.4 (R4.1)
unnamed: RN3.5 (R4.2), SW1.2
unnamed: RN4.2 (R2.1), SW1.3
unnamed: RN4.3 (R3.1), RN4.4 (R4.1)
unnamed: RN4.5 (R4.2), SW1.4

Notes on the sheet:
MIDI IN/OUT
12V IN + FUSING + DECOUPLING
ICSP
CONFIGURATION
SOLENOID SWITCHING
DC -> DC

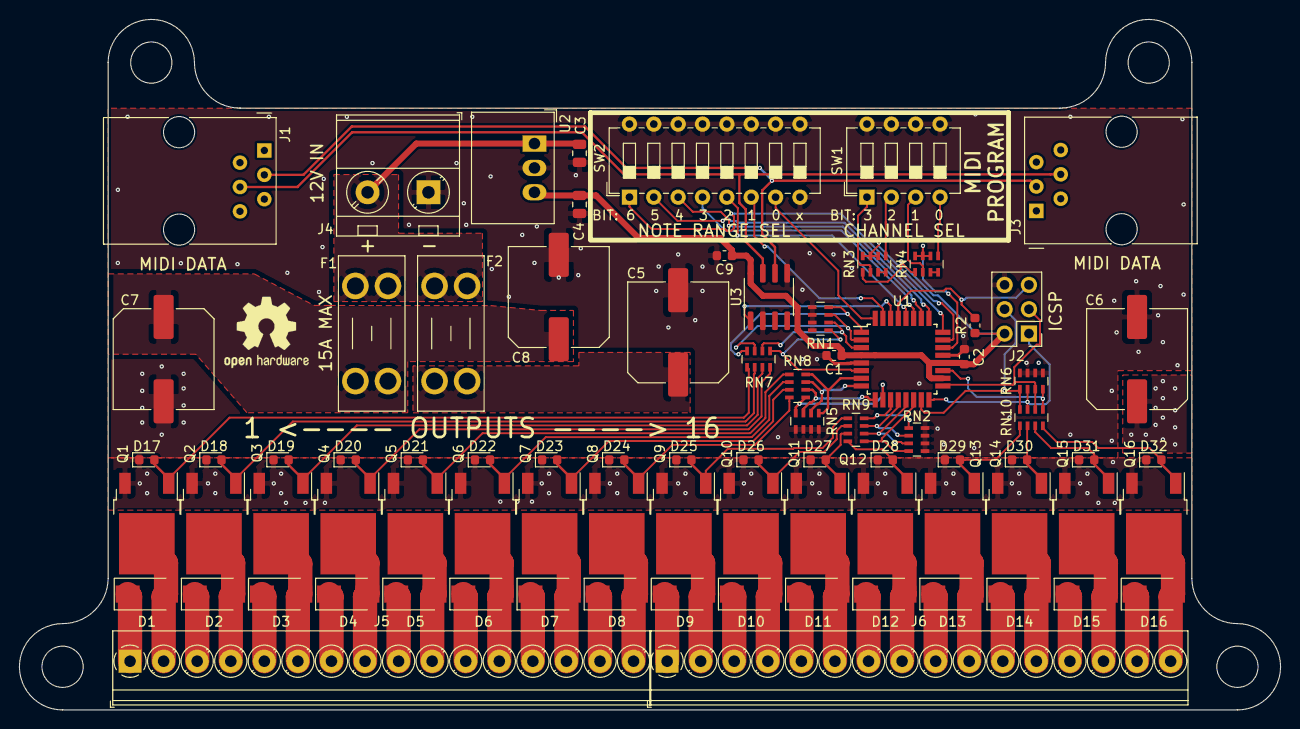
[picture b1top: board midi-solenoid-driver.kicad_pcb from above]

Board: 2 copper layers, 131.5 x 72.0 mm, 81 parts (0 on the bottom side), 72 nets.
